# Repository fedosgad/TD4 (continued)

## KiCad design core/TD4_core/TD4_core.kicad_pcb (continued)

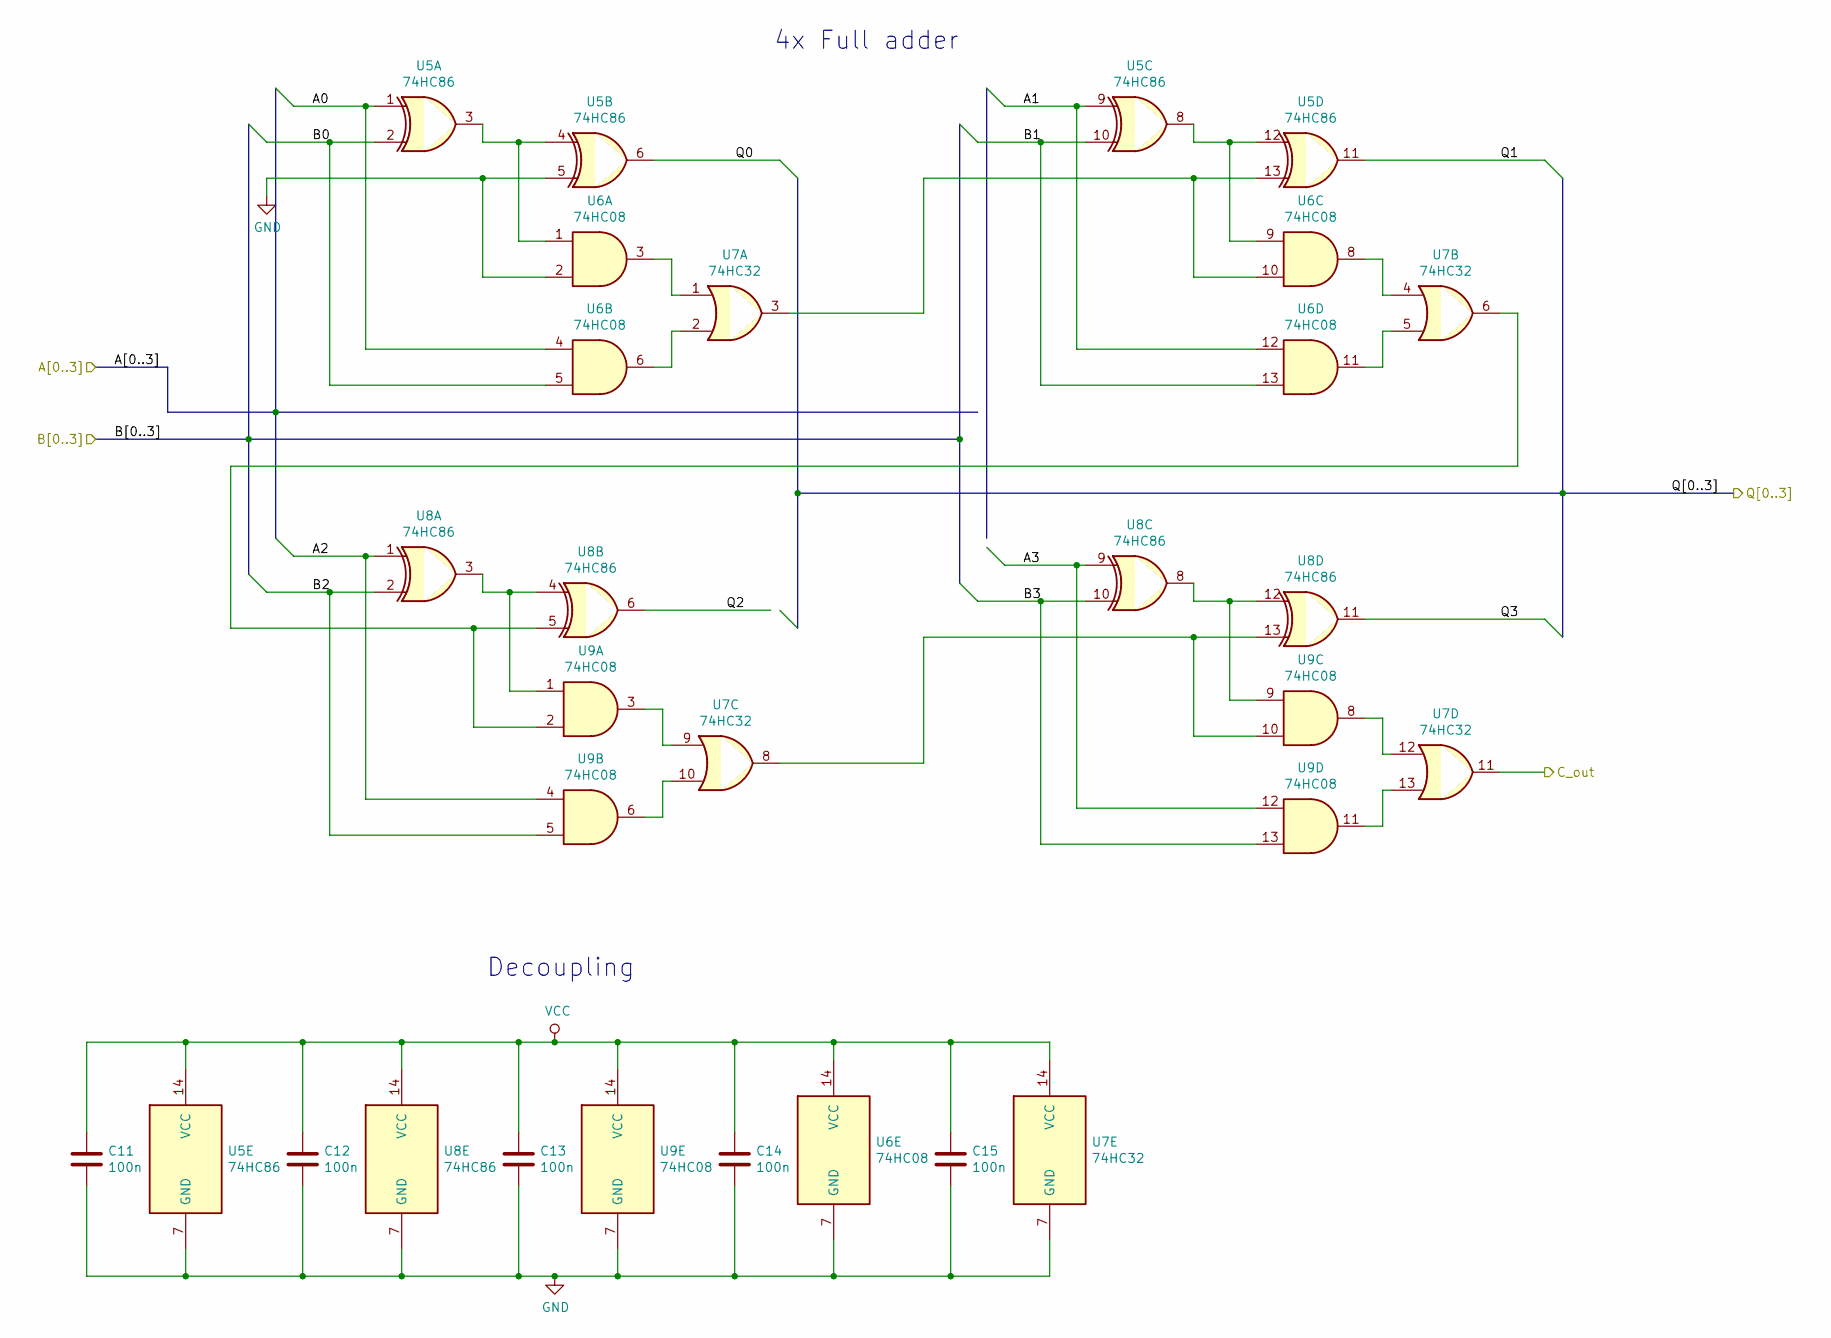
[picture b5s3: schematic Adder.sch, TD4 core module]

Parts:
C11, C12, C13, C14, C15: 100n; C_0805_2012Metric
U5, U8: 74HC86; SOIC-14_3.9x8.7mm_P1.27mm
U6, U9: 74HC08; SOIC-14_3.9x8.7mm_P1.27mm
U7: 74HC32; SOIC-14_3.9x8.7mm_P1.27mm

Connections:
/4-bit 3-state buffer/A0: U5.6; also elsewhere on the board
/4-bit 3-state buffer/A1: U5.11; also elsewhere on the board
/4-bit 3-state buffer/A2: U8.6; also elsewhere on the board
/4-bit 3-state buffer/A3: U8.11; also elsewhere on the board
/Adder/A0: U5.1, U6.4; also elsewhere on the board
/Adder/A1: U5.9, U6.12; also elsewhere on the board
/Adder/A2: U8.1, U9.4; also elsewhere on the board
/Adder/A3: U8.9, U9.12; also elsewhere on the board
/C_a: U7.11; also elsewhere on the board
unnamed: U5.3, U5.4, U6.1
unnamed: U5.8, U5.12, U6.9
unnamed: U5.13, U6.10, U7.3
unnamed: U6.3, U7.1
unnamed: U6.6, U7.2
unnamed: U6.8, U7.4
unnamed: U6.11, U7.5
unnamed: U7.6, U8.5, U9.2
unnamed: U7.8, U8.13, U9.10
unnamed: U7.9, U9.3
unnamed: U7.10, U9.6
unnamed: U7.12, U9.8
unnamed: U7.13, U9.11
unnamed: U8.3, U8.4, U9.1
unnamed: U8.8, U8.12, U9.9

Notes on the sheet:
Decoupling
4x Full adder

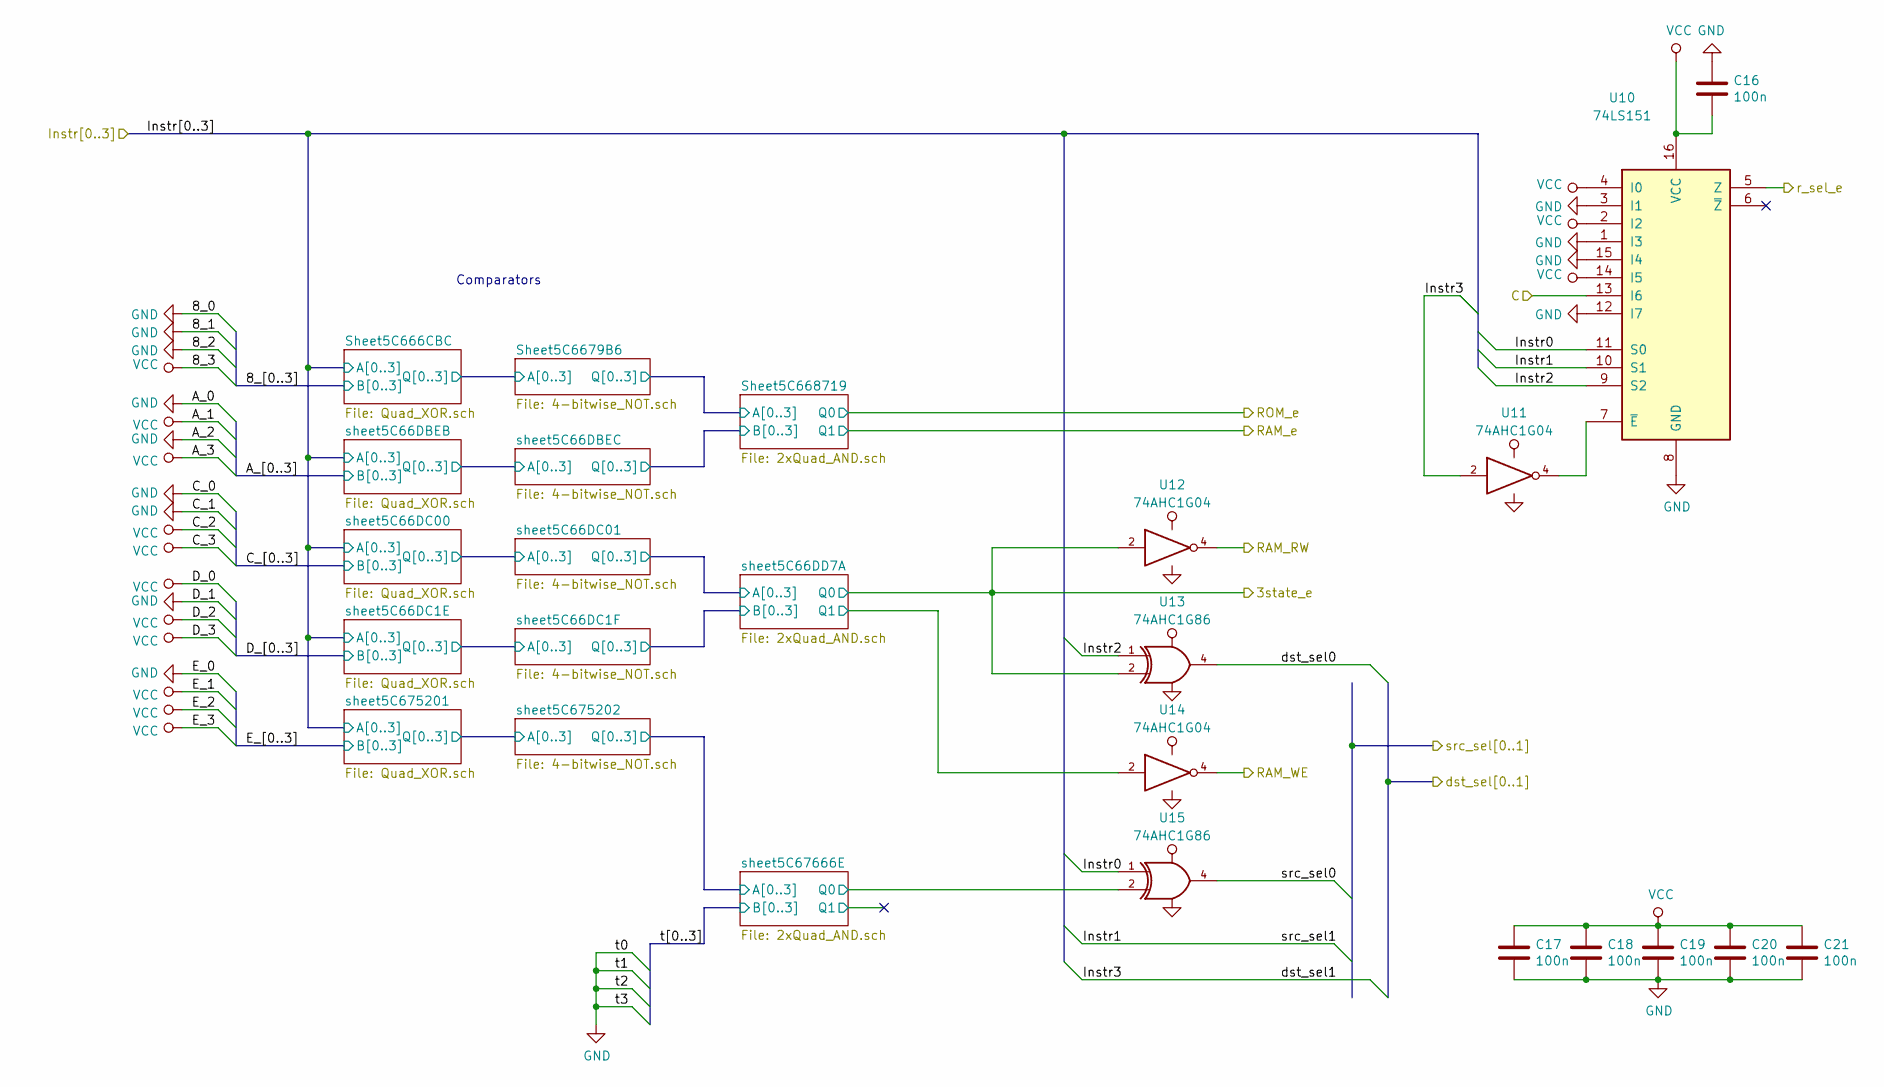
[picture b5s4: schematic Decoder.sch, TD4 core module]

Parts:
C16, C17, C18, C19, C20, C21: 100n; C_0805_2012Metric
U10: 74LS151; SOIC-16_3.9x9.9mm_P1.27mm
U11, U12, U14: 74AHC1G04; SOT-23-5
U13, U15: 74AHC1G86; SOT-23-5

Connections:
/C_r: U10.13 (I6); also elsewhere on the board
/Ins0: U10.11 (S0), U15.1; also elsewhere on the board
/Ins1: U10.10 (S1); also elsewhere on the board
/Ins2: U10.9 (S2), U13.1; also elsewhere on the board
/Ins3: U11.2; also elsewhere on the board
/Instruction decoder/3state_e: U12.2, U13.2; also elsewhere on the board
/Instruction decoder/sheet5C66DD7A/Q1: U14.2; also elsewhere on the board
/Instruction decoder/sheet5C67666E/Q0: U15.2; also elsewhere on the board
/Multiplexer 4x 4->1/Sel0: U15.4; also elsewhere on the board
/RAM_RW: U12.4; also elsewhere on the board
/RAM_WE: U14.4; also elsewhere on the board
/Register selector/Sel0: U13.4; also elsewhere on the board
/r_sel_e: U10.5 (Z); also elsewhere on the board
unnamed: U10.7 (~E), U11.4

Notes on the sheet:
Comparators

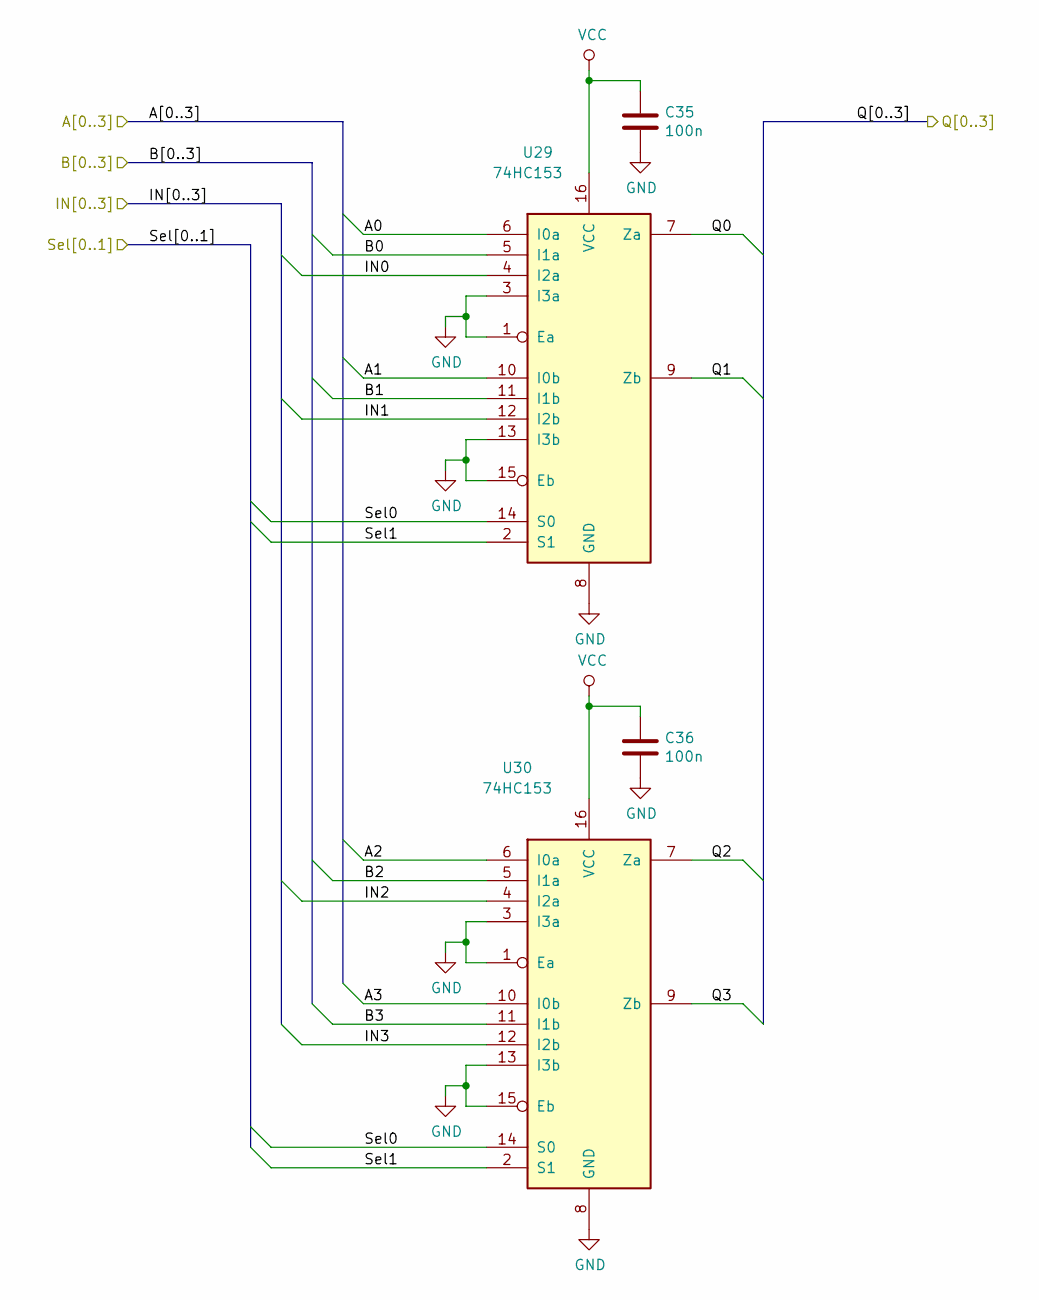
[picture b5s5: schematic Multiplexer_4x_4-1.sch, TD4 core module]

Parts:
C35, C36: 100n; C_0805_2012Metric
U29, U30: 74HC153; SOIC-16_3.9x9.9mm_P1.27mm

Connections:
/Adder/A0: U29.7 (Za); also elsewhere on the board
/Adder/A1: U29.9 (Zb); also elsewhere on the board
/Adder/A2: U30.7 (Za); also elsewhere on the board
/Adder/A3: U30.9 (Zb); also elsewhere on the board
/IN0: U29.4 (I2a); also elsewhere on the board
/IN1: U29.12 (I2b); also elsewhere on the board
/IN2: U30.4 (I2a); also elsewhere on the board
/IN3: U30.12 (I2b); also elsewhere on the board
/Ins1: U29.2 (S1), U30.2 (S1); also elsewhere on the board
/Multiplexer 4x 4->1/A0: U29.6 (I0a); also elsewhere on the board
/Multiplexer 4x 4->1/A1: U29.10 (I0b); also elsewhere on the board
/Multiplexer 4x 4->1/A2: U30.6 (I0a); also elsewhere on the board
/Multiplexer 4x 4->1/A3: U30.10 (I0b); also elsewhere on the board
/Multiplexer 4x 4->1/B0: U29.5 (I1a); also elsewhere on the board
/Multiplexer 4x 4->1/B1: U29.11 (I1b); also elsewhere on the board
/Multiplexer 4x 4->1/B2: U30.5 (I1a); also elsewhere on the board
/Multiplexer 4x 4->1/B3: U30.11 (I1b); also elsewhere on the board
/Multiplexer 4x 4->1/Sel0: U29.14 (S0), U30.14 (S0); also elsewhere on the board

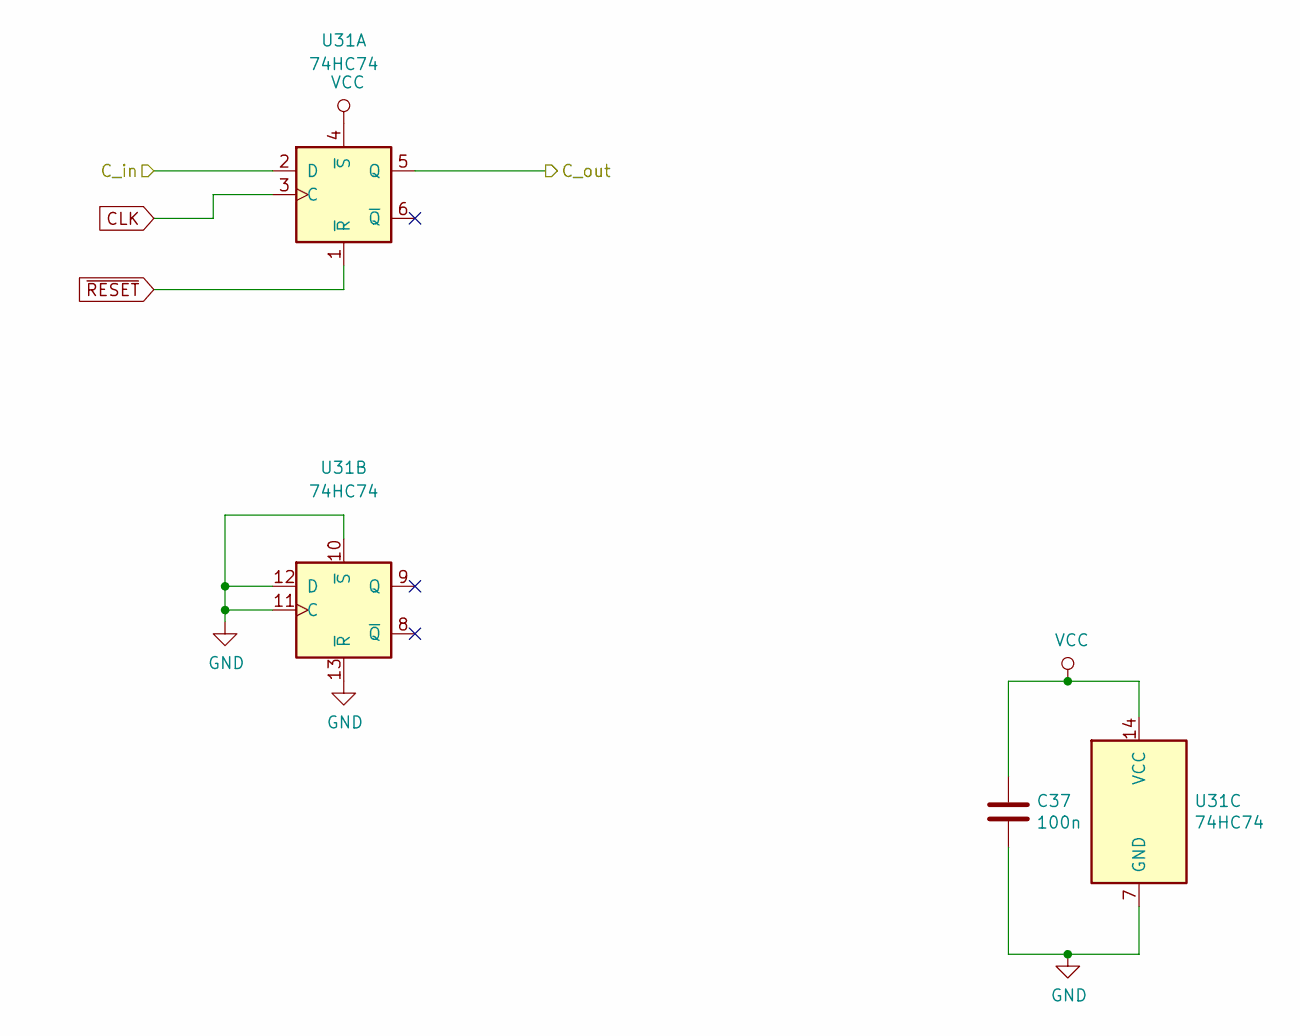
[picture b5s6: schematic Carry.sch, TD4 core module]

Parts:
C37: 100n; C_0805_2012Metric
U31: 74HC74; SOIC-14_3.9x8.7mm_P1.27mm

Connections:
/C_a: U31.2 (D); also elsewhere on the board
/C_r: U31.5 (Q); also elsewhere on the board
CLK: U31.3 (C); also elsewhere on the board
~RESET: U31.1 (~R); also elsewhere on the board

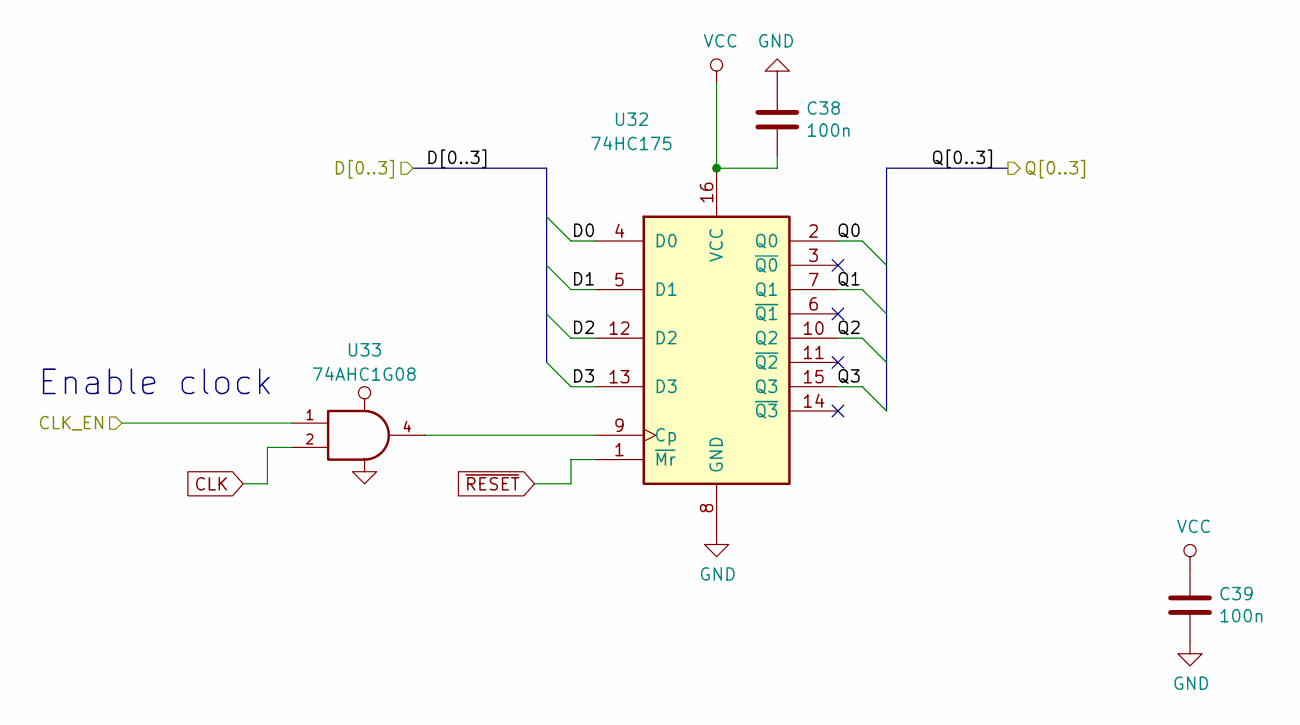
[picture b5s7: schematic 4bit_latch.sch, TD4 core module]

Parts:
C38, C39: 100n; C_0805_2012Metric
U32: 74HC175; SOIC-16_3.9x9.9mm_P1.27mm
U33: 74AHC1G08; SOT-23-5

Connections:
/4-bit latch/CLK_EN: U33.1; also elsewhere on the board
/ROM_A4: U32.2 (Q0); also elsewhere on the board
/ROM_A5: U32.7 (Q1); also elsewhere on the board
/ROM_A6: U32.10 (Q2); also elsewhere on the board
/ROM_A7: U32.15 (Q3); also elsewhere on the board
CLK: U33.2; also elsewhere on the board
unnamed: U32.9 (Cp), U33.4
~RESET: U32.1 (~Mr); also elsewhere on the board

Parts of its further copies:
C41, C42: 100n; C_0805_2012Metric
U35: 74HC175; SOIC-16_3.9x9.9mm_P1.27mm
U36: 74AHC1G08; SOT-23-5

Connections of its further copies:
/RAM_A4: U35.2 (Q0); also elsewhere on the board
/RAM_A5: U35.7 (Q1); also elsewhere on the board
/RAM_A6: U35.10 (Q2); also elsewhere on the board
/RAM_A7: U35.15 (Q3); also elsewhere on the board
/sheet5C68527E/CLK_EN: U36.1; also elsewhere on the board
CLK: U36.2; also elsewhere on the board
unnamed: U35.9 (Cp), U36.4
~RESET: U35.1 (~Mr); also elsewhere on the board

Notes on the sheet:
Enable clock

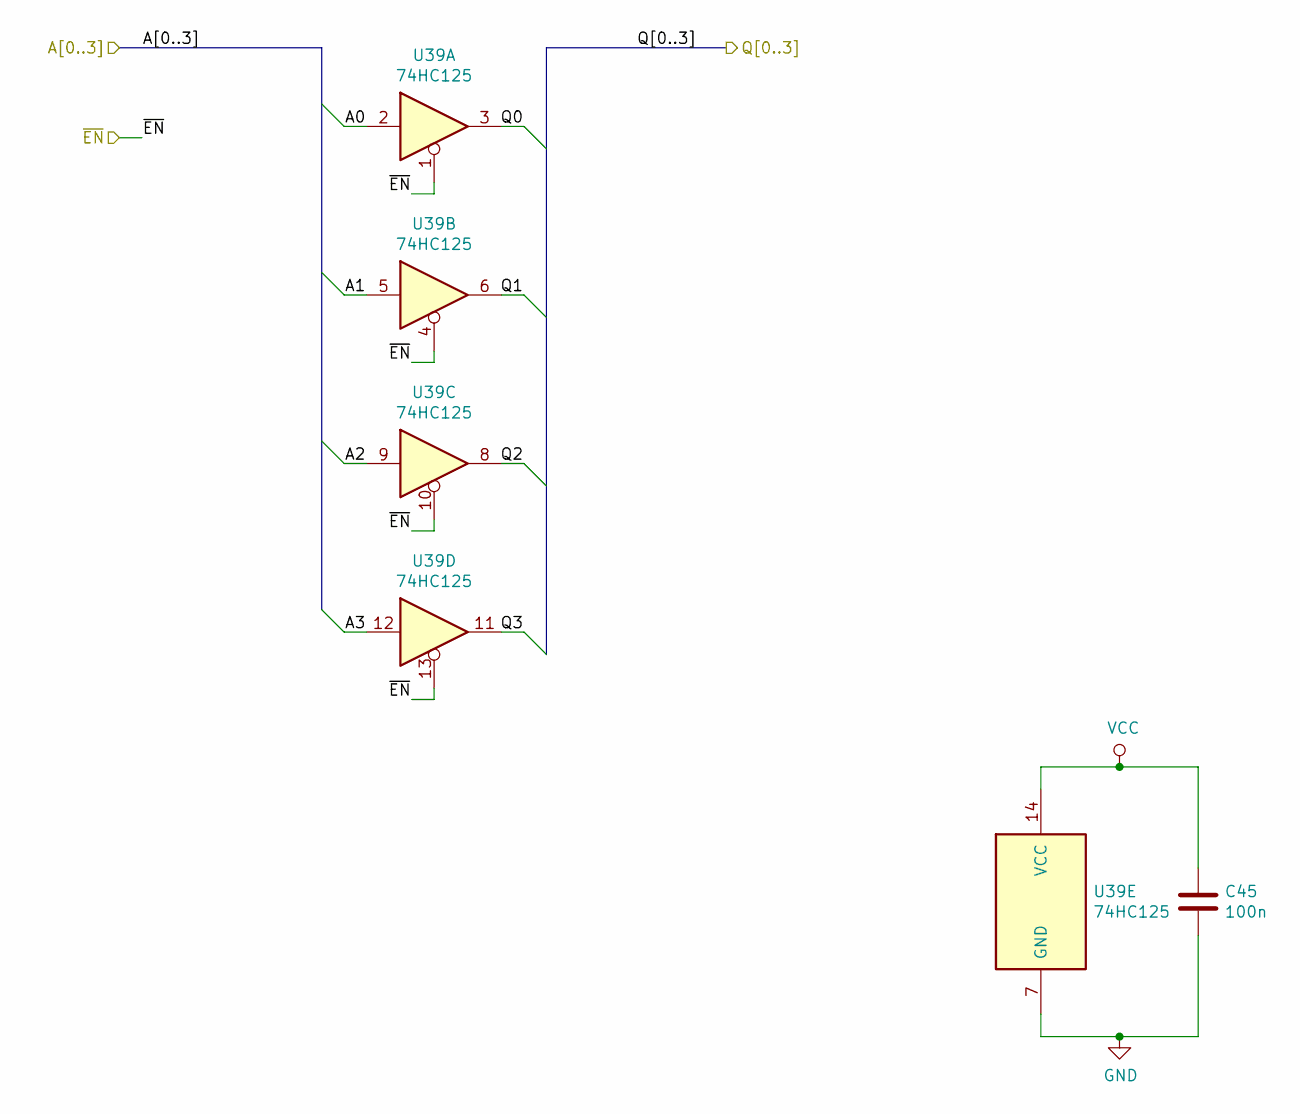
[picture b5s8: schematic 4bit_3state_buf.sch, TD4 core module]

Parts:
C40: 100n; C_0805_2012Metric
U34: 74HC125; SOIC-14_3.9x8.7mm_P1.27mm

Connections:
/4-bit 3-state buffer/A0: U34.2; also elsewhere on the board
/4-bit 3-state buffer/A1: U34.5; also elsewhere on the board
/4-bit 3-state buffer/A2: U34.9; also elsewhere on the board
/4-bit 3-state buffer/A3: U34.12; also elsewhere on the board
/Instruction decoder/3state_e: U34.1, U34.4, U34.10, U34.13; also elsewhere on the board
/RAM_D0: U34.3; also elsewhere on the board
/RAM_D1: U34.6; also elsewhere on the board
/RAM_D2: U34.8; also elsewhere on the board
/RAM_D3: U34.11; also elsewhere on the board

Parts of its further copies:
C44, C45, C46: 100n; C_0805_2012Metric
U38, U39, U40: 74HC125; SOIC-14_3.9x8.7mm_P1.27mm

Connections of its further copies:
/C_a: U40.2; also elsewhere on the board
/C_r: U40.5; also elsewhere on the board
/Multiplexer 4x 4->1/A0: U38.2; also elsewhere on the board
/Multiplexer 4x 4->1/A1: U38.5; also elsewhere on the board
/Multiplexer 4x 4->1/A2: U38.9; also elsewhere on the board
/Multiplexer 4x 4->1/A3: U38.12; also elsewhere on the board
/Multiplexer 4x 4->1/B0: U39.2; also elsewhere on the board
/Multiplexer 4x 4->1/B1: U39.5; also elsewhere on the board
/Multiplexer 4x 4->1/B2: U39.9; also elsewhere on the board
/Multiplexer 4x 4->1/B3: U39.12; also elsewhere on the board
/Sheet5C72E551/Out0: U38.3; also elsewhere on the board
/Sheet5C72E551/Out1: U38.6; also elsewhere on the board
/Sheet5C72E551/Out2: U38.8; also elsewhere on the board
/Sheet5C72E551/Out3: U38.11; also elsewhere on the board
/Sheet5C77FFEF/sheet5C78000E/Out0: U40.3; also elsewhere on the board
/Sheet5C77FFEF/sheet5C78000E/Out1: U40.6; also elsewhere on the board
/Sheet5C77FFEF/sheet5C78000E/Out2: U40.8; also elsewhere on the board
/Sheet5C77FFEF/sheet5C78000E/Out3: U40.11; also elsewhere on the board
/sheet5C74C5BC/Out0: U39.3; also elsewhere on the board
/sheet5C74C5BC/Out1: U39.6; also elsewhere on the board
/sheet5C74C5BC/Out2: U39.8; also elsewhere on the board
/sheet5C74C5BC/Out3: U39.11; also elsewhere on the board
/~DEBUG_ON~: U38.1, U38.4, U38.10, U38.13, U39.1, U39.4, U39.10, U39.13, U40.1, U40.4, U40.10, U40.13; also elsewhere on the board

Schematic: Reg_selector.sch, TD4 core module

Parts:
C43: 100n; C_0805_2012Metric
U37: 74HC155; SOIC-16_3.9x9.9mm_P1.27mm

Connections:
/Ins3: U37.3 (A1); also elsewhere on the board
/Register selector/Q0: U37.7 (Q0a); also elsewhere on the board
/Register selector/Q1: U37.6 (Q1a); also elsewhere on the board
/Register selector/Q2: U37.5 (Q2a); also elsewhere on the board
/Register selector/Q3: U37.4 (Q3a); also elsewhere on the board
/Register selector/Sel0: U37.13 (A0); also elsewhere on the board
/r_sel_e: U37.2 (Ea2); also elsewhere on the board

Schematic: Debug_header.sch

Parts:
J2: Conn_01x04; PinHeader_1x04_P2.54mm_Horizontal

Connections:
/Sheet5C72E551/Out0: J2.1; also elsewhere on the board
/Sheet5C72E551/Out1: J2.2; also elsewhere on the board
/Sheet5C72E551/Out2: J2.3; also elsewhere on the board
/Sheet5C72E551/Out3: J2.4; also elsewhere on the board

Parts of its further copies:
J3, J4: Conn_01x04; PinHeader_1x04_P2.54mm_Horizontal

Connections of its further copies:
/Sheet5C77FFEF/sheet5C78000E/Out0: J4.1; also elsewhere on the board
/Sheet5C77FFEF/sheet5C78000E/Out1: J4.2; also elsewhere on the board
/Sheet5C77FFEF/sheet5C78000E/Out2: J4.3; also elsewhere on the board
/Sheet5C77FFEF/sheet5C78000E/Out3: J4.4; also elsewhere on the board
/sheet5C74C5BC/Out0: J3.1; also elsewhere on the board
/sheet5C74C5BC/Out1: J3.2; also elsewhere on the board
/sheet5C74C5BC/Out2: J3.3; also elsewhere on the board
/sheet5C74C5BC/Out3: J3.4; also elsewhere on the board

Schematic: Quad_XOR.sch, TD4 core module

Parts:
C22: 100n; C_0805_2012Metric
U16: 74HC86; SOIC-14_3.9x8.7mm_P1.27mm

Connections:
/Ins0: U16.1; also elsewhere on the board
/Ins1: U16.4; also elsewhere on the board
/Ins2: U16.9; also elsewhere on the board
/Ins3: U16.12; also elsewhere on the board
/Instruction decoder/Sheet5C6679B6/A0: U16.3; also elsewhere on the board
/Instruction decoder/Sheet5C6679B6/A1: U16.6; also elsewhere on the board
/Instruction decoder/Sheet5C6679B6/A2: U16.8; also elsewhere on the board
/Instruction decoder/Sheet5C6679B6/A3: U16.11; also elsewhere on the board

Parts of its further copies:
C25, C27, C29, C32: 100n; C_0805_2012Metric
U19, U21, U23, U26: 74HC86; SOIC-14_3.9x8.7mm_P1.27mm

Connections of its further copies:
/Ins0: U19.1, U21.1, U23.1, U26.1; also elsewhere on the board
/Ins1: U19.4, U21.4, U23.4, U26.4; also elsewhere on the board
/Ins2: U19.9, U21.9, U23.9, U26.9; also elsewhere on the board
/Ins3: U19.12, U21.12, U23.12, U26.12; also elsewhere on the board
/Instruction decoder/sheet5C66DBEC/A0: U19.3; also elsewhere on the board
/Instruction decoder/sheet5C66DBEC/A1: U19.6; also elsewhere on the board
/Instruction decoder/sheet5C66DBEC/A2: U19.8; also elsewhere on the board
/Instruction decoder/sheet5C66DBEC/A3: U19.11; also elsewhere on the board
/Instruction decoder/sheet5C66DC01/A0: U21.3; also elsewhere on the board
/Instruction decoder/sheet5C66DC01/A1: U21.6; also elsewhere on the board
/Instruction decoder/sheet5C66DC01/A2: U21.8; also elsewhere on the board
/Instruction decoder/sheet5C66DC01/A3: U21.11; also elsewhere on the board
/Instruction decoder/sheet5C66DC1F/A0: U23.3; also elsewhere on the board
/Instruction decoder/sheet5C66DC1F/A1: U23.6; also elsewhere on the board
/Instruction decoder/sheet5C66DC1F/A2: U23.8; also elsewhere on the board
/Instruction decoder/sheet5C66DC1F/A3: U23.11; also elsewhere on the board
/Instruction decoder/sheet5C675202/A0: U26.3; also elsewhere on the board
/Instruction decoder/sheet5C675202/A1: U26.6; also elsewhere on the board
/Instruction decoder/sheet5C675202/A2: U26.8; also elsewhere on the board
/Instruction decoder/sheet5C675202/A3: U26.11; also elsewhere on the board

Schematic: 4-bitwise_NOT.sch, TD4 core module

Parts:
C23: 100n; C_0805_2012Metric
U17: 74HC04; SOIC-14_3.9x8.7mm_P1.27mm

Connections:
/Instruction decoder/Sheet5C6679B6/A0: U17.1; also elsewhere on the board
/Instruction decoder/Sheet5C6679B6/A1: U17.3; also elsewhere on the board
/Instruction decoder/Sheet5C6679B6/A2: U17.5; also elsewhere on the board
/Instruction decoder/Sheet5C6679B6/A3: U17.9; also elsewhere on the board
/Instruction decoder/Sheet5C668719/A0: U17.2; also elsewhere on the board
/Instruction decoder/Sheet5C668719/A1: U17.4; also elsewhere on the board
/Instruction decoder/Sheet5C668719/A2: U17.6; also elsewhere on the board
/Instruction decoder/Sheet5C668719/A3: U17.8; also elsewhere on the board

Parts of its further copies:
C26, C28, C30, C33: 100n; C_0805_2012Metric
U20, U22, U24, U27: 74HC04; SOIC-14_3.9x8.7mm_P1.27mm

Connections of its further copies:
/Instruction decoder/Sheet5C668719/B0: U20.2; also elsewhere on the board
/Instruction decoder/Sheet5C668719/B1: U20.4; also elsewhere on the board
/Instruction decoder/Sheet5C668719/B2: U20.6; also elsewhere on the board
/Instruction decoder/Sheet5C668719/B3: U20.8; also elsewhere on the board
/Instruction decoder/sheet5C66DBEC/A0: U20.1; also elsewhere on the board
/Instruction decoder/sheet5C66DBEC/A1: U20.3; also elsewhere on the board
/Instruction decoder/sheet5C66DBEC/A2: U20.5; also elsewhere on the board
/Instruction decoder/sheet5C66DBEC/A3: U20.9; also elsewhere on the board
/Instruction decoder/sheet5C66DC01/A0: U22.1; also elsewhere on the board
/Instruction decoder/sheet5C66DC01/A1: U22.3; also elsewhere on the board
/Instruction decoder/sheet5C66DC01/A2: U22.5; also elsewhere on the board
/Instruction decoder/sheet5C66DC01/A3: U22.9; also elsewhere on the board
/Instruction decoder/sheet5C66DC1F/A0: U24.1; also elsewhere on the board
/Instruction decoder/sheet5C66DC1F/A1: U24.3; also elsewhere on the board
/Instruction decoder/sheet5C66DC1F/A2: U24.5; also elsewhere on the board
/Instruction decoder/sheet5C66DC1F/A3: U24.9; also elsewhere on the board
/Instruction decoder/sheet5C66DD7A/A0: U22.2; also elsewhere on the board
/Instruction decoder/sheet5C66DD7A/A1: U22.4; also elsewhere on the board
/Instruction decoder/sheet5C66DD7A/A2: U22.6; also elsewhere on the board
/Instruction decoder/sheet5C66DD7A/A3: U22.8; also elsewhere on the board
/Instruction decoder/sheet5C66DD7A/B0: U24.2; also elsewhere on the board
/Instruction decoder/sheet5C66DD7A/B1: U24.4; also elsewhere on the board
/Instruction decoder/sheet5C66DD7A/B2: U24.6; also elsewhere on the board
/Instruction decoder/sheet5C66DD7A/B3: U24.8; also elsewhere on the board
/Instruction decoder/sheet5C67666E/A0: U27.2; also elsewhere on the board
/Instruction decoder/sheet5C67666E/A1: U27.4; also elsewhere on the board
/Instruction decoder/sheet5C67666E/A2: U27.6; also elsewhere on the board
/Instruction decoder/sheet5C67666E/A3: U27.8; also elsewhere on the board
/Instruction decoder/sheet5C675202/A0: U27.1; also elsewhere on the board
/Instruction decoder/sheet5C675202/A1: U27.3; also elsewhere on the board
/Instruction decoder/sheet5C675202/A2: U27.5; also elsewhere on the board
/Instruction decoder/sheet5C675202/A3: U27.9; also elsewhere on the board

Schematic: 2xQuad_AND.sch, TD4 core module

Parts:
C24: 100n; C_0805_2012Metric
U18: 74HC21; SOIC-14_3.9x8.7mm_P1.27mm

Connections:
/4-bit latch/CLK_EN: U18.6; also elsewhere on the board
/Instruction decoder/Sheet5C668719/A0: U18.1; also elsewhere on the board
/Instruction decoder/Sheet5C668719/A1: U18.2; also elsewhere on the board
/Instruction decoder/Sheet5C668719/A2: U18.4; also elsewhere on the board
/Instruction decoder/Sheet5C668719/A3: U18.5; also elsewhere on the board
/Instruction decoder/Sheet5C668719/B0: U18.9; also elsewhere on the board
/Instruction decoder/Sheet5C668719/B1: U18.10; also elsewhere on the board
/Instruction decoder/Sheet5C668719/B2: U18.12; also elsewhere on the board
/Instruction decoder/Sheet5C668719/B3: U18.13; also elsewhere on the board
/sheet5C68527E/CLK_EN: U18.8; also elsewhere on the board

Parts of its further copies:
C31, C34: 100n; C_0805_2012Metric
U25, U28: 74HC21; SOIC-14_3.9x8.7mm_P1.27mm

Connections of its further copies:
/Instruction decoder/3state_e: U25.6; also elsewhere on the board
/Instruction decoder/sheet5C66DD7A/A0: U25.1; also elsewhere on the board
/Instruction decoder/sheet5C66DD7A/A1: U25.2; also elsewhere on the board
/Instruction decoder/sheet5C66DD7A/A2: U25.4; also elsewhere on the board
/Instruction decoder/sheet5C66DD7A/A3: U25.5; also elsewhere on the board
/Instruction decoder/sheet5C66DD7A/B0: U25.9; also elsewhere on the board
/Instruction decoder/sheet5C66DD7A/B1: U25.10; also elsewhere on the board
/Instruction decoder/sheet5C66DD7A/B2: U25.12; also elsewhere on the board
/Instruction decoder/sheet5C66DD7A/B3: U25.13; also elsewhere on the board
/Instruction decoder/sheet5C66DD7A/Q1: U25.8; also elsewhere on the board
/Instruction decoder/sheet5C67666E/A0: U28.1; also elsewhere on the board
/Instruction decoder/sheet5C67666E/A1: U28.2; also elsewhere on the board
/Instruction decoder/sheet5C67666E/A2: U28.4; also elsewhere on the board
/Instruction decoder/sheet5C67666E/A3: U28.5; also elsewhere on the board
/Instruction decoder/sheet5C67666E/Q0: U28.6; also elsewhere on the board
/Instruction decoder/sheet5C67666E/Q1: U28.8

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
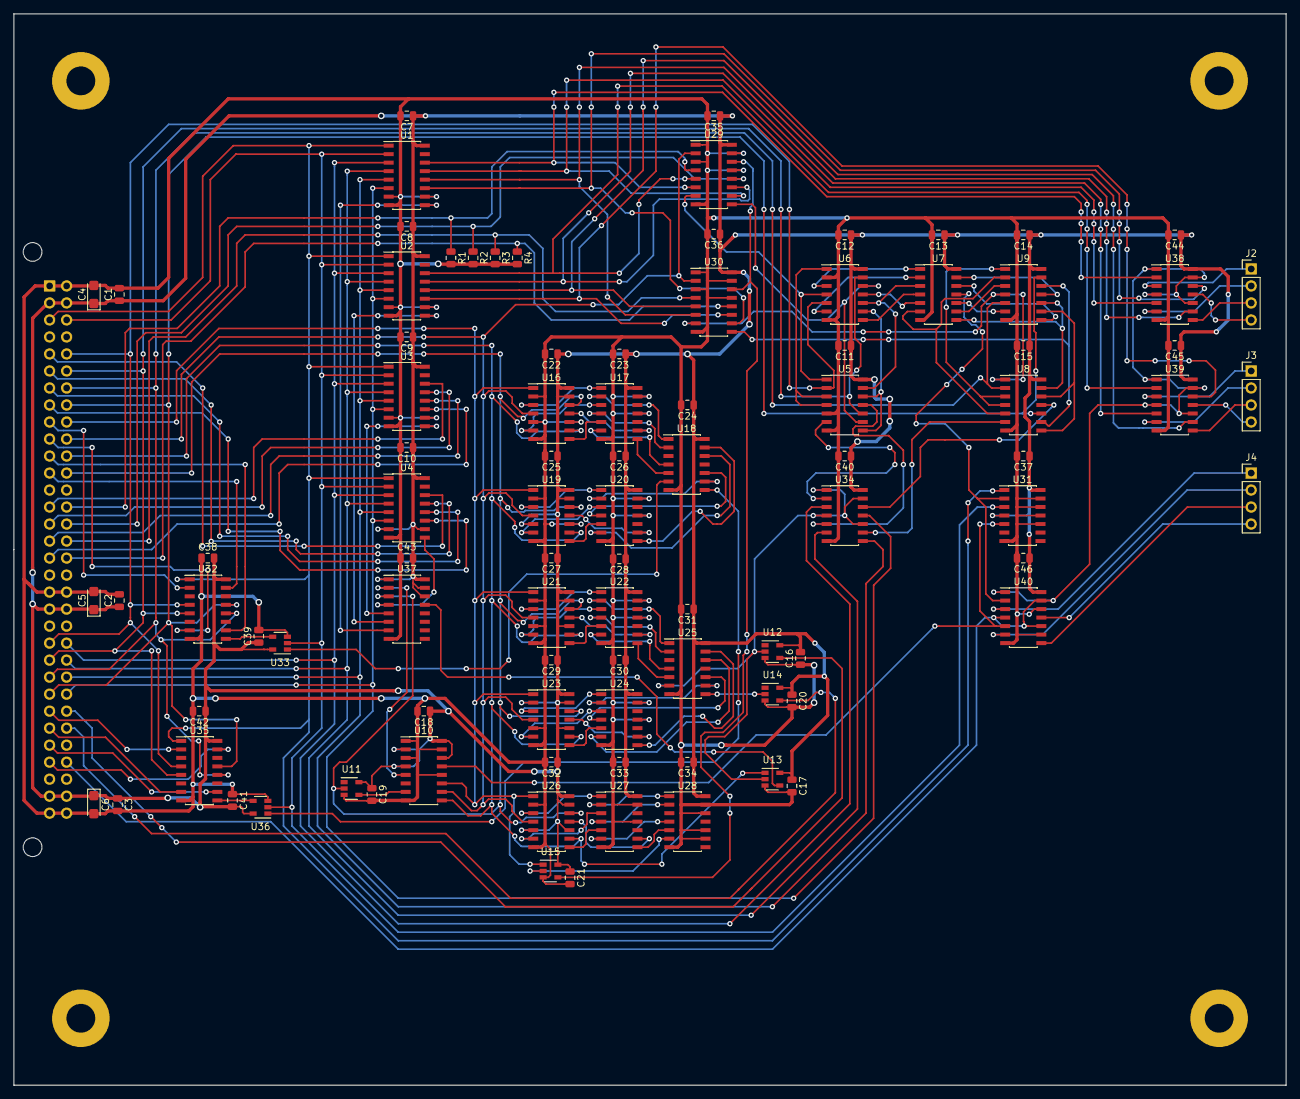
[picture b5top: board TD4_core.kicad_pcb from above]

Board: 2 copper layers, 190.0 x 160.0 mm, 94 parts (1 on the bottom side), 139 nets.

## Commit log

2019-02-06 Work already done
2019-02-07 Started with RAM
2019-02-07 Address decoder done
2019-02-08 RAM done (sort of)
2019-02-08 ROM done
2019-02-08 Started refactoring
2019-02-08 RAM refactoring goes on
2019-02-08 RAM done (damn buses\!)
2019-02-08 ROM refactoring done
2019-02-08 Main core schematic done; only decoder left
2019-02-12 Core assembled; decoder left
2019-02-14 Decoder done (finally!)
2019-02-17 Core schematic done. Backplane connector added, including separate .sch file to append.
2019-02-18 Added debug headers to core
2019-02-18 Added backplane connectors to all PCBs
2019-02-18 Started with backplane
2019-02-18 Fixed minor core PCB errors
2019-02-19 Added IN bus pull-ups in core
2019-02-20 Started routing core PCB
2019-02-20 Adder and decoder done
2019-02-20 Minor core blocks routed
2019-02-20 Routed most of data path
2019-02-20 Started tieing it all together
2019-02-21 Core routed
2019-02-21 DRC violations fixed; edge cuts added
2019-02-21 Replaced debug headers with vertical ones
2019-02-21 Minor changes to PCB
2019-02-26 Main RAM blocks routed
2019-02-27 RAM routing done
2019-03-18 ROM routing done
2019-03-20 Backplane routed
2019-03-23 Clock/reset PCB routed
2019-03-26 Added 6th slot to the backplane
2019-03-29 Made front panel circuit
2019-06-07 Added SystemVerilog code for vanilla TD4
